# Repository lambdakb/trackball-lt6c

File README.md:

# LT6C 6 Keys Trackball

The LambdaKB LT6C is a re-creation of the [Ploopy Adept](https://ploopy.co/adept-trackball/) PCB and case as an easy to build DIY kit. The main goal was to build it using only off-the-shelf part and components that can be hand soldered relatively easily.

We set out to create a more affordable alternative to the original Adept trackball while retaining all its features, primarily for individuals in regions where purchasing the original kit isn't cost-effective (for example, shipping from the Ploopy store to Europe costs over €35 before import taxes).

## PCB

|             Front             |            Back             |
| :---------------------------: | :-------------------------: |
| [![PCB Front]][PCB Front PNG] | [![PCB Back]][PCB Back PNG] |

[PCB Front]: output/img/lt6c-pcb-top.svg
[PCB Front PNG]: output/img/lt6c-pcb-top.png
[PCB Back]: output/img/lt6c-pcb-bottom.svg
[PCB Back PNG]: output/img/lt6c-pcb-bottom.png

The PCB has been designed in [KiCad EDA 9.0](https://www.kicad.org/) using the [`kicad-lkbd`](https://github.com/lambdakb/kicad-lkbd) libraries.

You can preview the project files using [KiCanvas](https://kicanvas.org/?github=https%3A%2F%2Fgithub.com%2Flambdakb%2Ftrackball-lt6c%2Fblob%2Fmain%2Fpcb%2Flt6c-pcb.kicad_pro) directly in your browser and download the latest fabrication files for JLCPCB from the [latest release](https://github.com/lambdakb/trackball-lt6c/releases/latest/).

The exported schematic is also available under [`output/schematics`](output/schematics/).

### PCB Order

| Parameters                       | Value                  |
| -------------------------------- | ---------------------- |
| Base Material                    | FR4                    |
| Layers                           | 2                      |
| Dimensions                       | 62 × 64.4 mm           |
| PCB Thickness                    | 0.8 mm                 |
| PCB Color [^pcb-color]           | Green                  |
| Silkscreen                       | White                  |
| Surface Finish [^surface-finish] | Lead Free HASL or ENIG |
| Copper Weight                    | 1 oz                   |
| Via Covering                     | Tented                 |
| Min Via Hole Size                | 0.3 mm                 |
| Board Outline Tolerance          | ± 0.2 mm               |

[^pcb-color]: You can select any PCB color you want but manufacturers such as JLCPCB will charge you more for it as the combo 0.8 mm thickness, Lead Free HASL surface finish and alternative board color is pretty uncommon for them to produce.
[^surface-finish]: The "HASL (with lead)" option is extremely discouraged due to the risk of lead poisoning. We strongly recommend paying the premium for the "Lead Free HASL" option.

## Case

|                                                3D Render                                                 |
| :------------------------------------------------------------------------------------------------------: |
|  |

A 3D printed case is available under [`case`](case/), this is a simple modification of the original [Ploopy Adept's case](https://github.com/ploopyco/adept-trackball/tree/master/hardware/mechanicals) that adds clearance for the back of our PCB. No other major modification has been done it.

This includes:

- A pre-cconfigured [`3mf` file](case/lt6c-case.3mf) for Orca Slicer
- Printing instructions
- Individual STL files, STEP file, and the original Fusion 360 project archive

Feel free to modify the case to your liking, but please make sure to respect the original [license](./README.md#license) when doing so.

## BOM

| Part                          | Ref.                                 | Quantity | Remarks                                                                                                                                         |
| ----------------------------- | ------------------------------------ | :------: | ----------------------------------------------------------------------------------------------------------------------------------------------- |
| PCB                           | [LT6C PCB](./README.md#pcb)          |    1     | See [PCB](./README.md#pcb) section on how to order it.                                                                                          |
| 3D Printed Case               | [LT6C Case](./case/README.md)        |    1     | 3D Printed case adapted from the [Adept Trackball case]. Make sure to check its individual [BOM](case/README.md#bom) for the required hardware. |
| 44 mm Trackball               | Any [1.75" Snooker Ball]             |    1     | The trackball ball itself, any 1.75" snooker / billiard ball should work.                                                                       |
| XIAO RP2040 Controller        | [SeeedStudio XIAO RP2040]            |    1     | Main controller for QMK/Vial.                                                                                                                   |
| Micro Switches                | [D2LS-21 SMD Micro Switch]           |    6     | Micro switches for mouse buttons.                                                                                                               |
| PMW3360 Optical Sensor & Lens | [PMW3360DM-T2QU + LM19-LSI]          |    1     | Optical mouse sensor and lens used to detect trackball movement.                                                                                |
| 1.8V DO                       | [TPS76318 Fixed 1.8V LDO (SOT-23-5)] |    1     | Power regulator for optical sensor.                                                                                                             |
| 1uF Capacitor                 | [0805 SMD Ceramic Capacitor]         |    1     | Required by the optical sensor LDO.                                                                                                             |
| 4.7uF Capacitors              | [0805 SMD Ceramic Capacitor]         |    2     | Power filtering capacitor for optical sensor and required LDO.                                                                                  |
| 100nF Capacitors              | [0805 SMD Ceramic Capacitor]         |    1     | Power filtering for the optical sensor.                                                                                                         |
| 10K Ω Resistor                | [0805 SMD Resistor]                  |    1     | Required by the optical sensor.                                                                                                                 |
| 39 Ω Resistor                 | [0805 SMD Resistor]                  |    1     | Required by the optical sensor.                                                                                                                 |

[Adept Trackball case]: https://github.com/ploopyco/adept-trackball/tree/master/hardware/mechanicals
[1.75" Snooker Ball]: https://amzn.eu/d/hGChcvq
[SeeedStudio XIAO RP2040]: https://www.seeedstudio.com/XIAO-RP2040-v1-0-p-5026.html
[D2LS-21 SMD Micro Switch]: https://www.aliexpress.com/item/1005003435671261.html
[PMW3360DM-T2QU + LM19-LSI]: https://www.aliexpress.com/item/4000904265601.html?
[TPS76318 Fixed 1.8V LDO (SOT-23-5)]: https://www.aliexpress.com/item/1005007852956393.html
[0805 SMD Ceramic Capacitor]: https://www.aliexpress.com/item/32812155708.html
[0805 SMD Resistor]: https://www.aliexpress.com/item/32847143167.html

## Firmware

Firmware has been built using [Vial](https://get.vial.today/), a fork of [QMK](https://qmk.fm) allowing configuration through a nice GUI.

|                                                        Layout                                                         |
| :-------------------------------------------------------------------------------------------------------------------: |
|  |

Sources are available in our own [`lambdakb/vial-qmk`](hhttps://github.com/lambdakb/vial-qmk/tree/lambdakb/keyboards/lambdakb/lt6c) repository and can be built using the [QMK CLI](https://docs.qmk.fm/cli).

```sh
# Clone the repository
git clone --recursive https://github.com/lambdakb/vial-qmk.git
# Compile the firmware
cd vial-qmk
qmk compile -kb lambdakb/lt6c -km vial
# Shoudl generate a `lambdakb_lt6c_vial.uf2` file at the root of the repository.
```

To flash the firmware to your trackball, follow the following steps:

- Put the XIAO RP2040 in Bootloader mode by holding the BOOT button while plugging the USB cable (see [official guide](https://wiki.seeedstudio.com/XIAO-RP2040/#enter-bootloader-mode) if you need help).
- Mount the `RPI-RP2` drive on your computer.
- Copy or drag and drop the `lambdakb_lt6c_vial.uf2` file to the `RPI-RP2` drive.
- The trackball should now reboot, and the firmware should be flashed.
- Open the [Vial Desktop Application](https://config.vial.today/) or [Vial Web App](https://vial.rocks/app/) to configure the trackball.

> [!NOTE]
> To allow the firmware to be updated without requiring disassembly, you can enter Bootloader mode by holding the bottom left key of the trackball and plugging the USB cable. This is only possible after the firmware has been flashed the first time.

## Attribution

This project is a complete reimplementation of the [Ploopy Adept trackball](https://ploopy.co/adept-trackball/) PCB using off-the-shelf components that are relatively easy to hand solder.

The provided [3D printed case](#case) is a modification of [the Adept's original case](https://github.com/ploopyco/adept-trackball/tree/master/hardware/mechanicals) with a bit more space at the back to fit the new controller on the PCB. It has otherwise not be modified.

The original concept and design were created by Ploopy, who have licensed it under the [CERN Open Hardware Licence Version 2 – Strongly Reciprocal (CERN-OHL-S-2.0)](https://github.com/ploopyco/adept-trackball/blob/master/LICENSE), which permits adaptations, as demonstrated in this project.

## License

This design is licensed under the [CERN Open Hardware Licence Version 2 – Strongly Reciprocal (CERN-OHL-S-2.0)](https://opensource.org/license/cern-ohl-s).

You are free to use, modify, and distribute this design for any purpose, provided that:

- **Attribution**: Appropriate credit is given, a link to the license is provided, and any modifications are clearly indicated.
- **Reciprocity**: Any derivative works must be released under the same license.

If you are a retailer or business interested in producing or selling this design or related products, I’d love to discuss it! Please feel free to reach out so we can explore potential arrangements.

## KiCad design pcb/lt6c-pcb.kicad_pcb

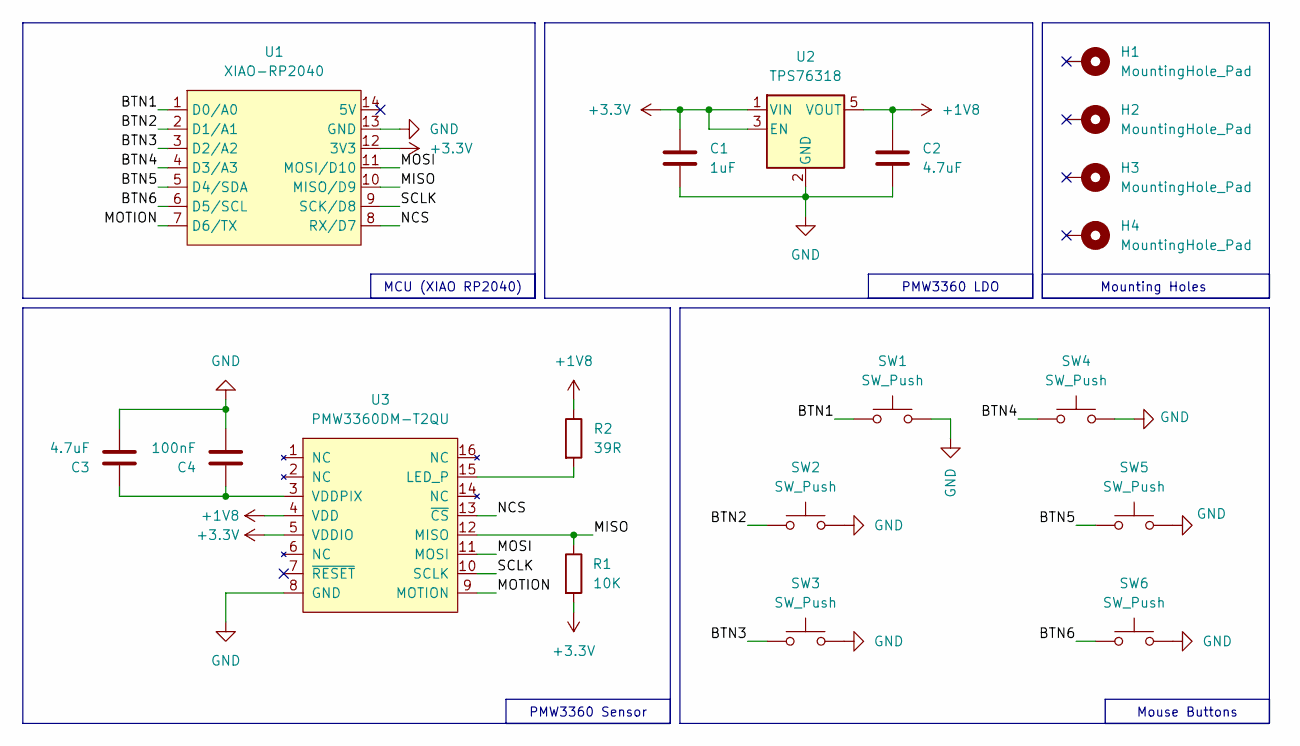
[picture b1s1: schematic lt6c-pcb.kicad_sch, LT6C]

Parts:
C1: 1uF; C_0805_2012Metric_Pad1.18x1.45mm_HandSolder; JLC 0805
C2, C3: 4.7uF; C_0805_2012Metric_Pad1.18x1.45mm_HandSolder; JLC 0805
C4: 100nF; C_0805_2012Metric_Pad1.18x1.45mm_HandSolder; JLC 0805
H1, H2, H3, H4: MountingHole_Pad; MountingHole_2.2mm_M2_ISO14580_Pad
R1: 10K; R_0805_2012Metric_Pad1.20x1.40mm_HandSolder; JLC 0805
R2: 39R; R_0805_2012Metric_Pad1.20x1.40mm_HandSolder; JLC 0805
SW1, SW2, SW3, SW4, SW5, SW6: SW_Push; SW_D2LS_OMR; JLC D2LS
U1: XIAO-RP2040; MCU_XIAO-RP2040
U2: TPS76318; SOT-23-5; JLC SOT-23-5
U3: PMW3360DM-T2QU; JLC DIP-16

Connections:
+1V8: C2.2, R2.1, U2.5 (VOUT), U3.4 (VDD)
+3.3V: C1.2, R1.2, U1.12 (3V3), U2.1 (VIN), U2.3 (EN), U3.5 (VDDIO)
/BTN1: SW1.1, U1.1 (D0/A0)
/BTN2: SW2.1, U1.2 (D1/A1)
/BTN3: SW3.1, U1.3 (D2/A2)
/BTN4: SW4.1, U1.4 (D3/A3)
/BTN5: SW5.1, U1.5 (D4/SDA)
/BTN6: SW6.1, U1.6 (D5/SCL)
/MISO: R1.1, U1.10 (MISO/D9), U3.12 (MISO)
/MOSI: U1.11 (MOSI/D10), U3.11 (MOSI)
/MOTION: U1.7 (D6/TX), U3.9 (MOTION)
/NCS: U1.8 (RX/D7), U3.13 (~CS)
/SCLK: U1.9 (SCK/D8), U3.10 (SCLK)
GND: C1.1, C2.1, C3.1, C4.1, SW1.2, SW2.2, SW3.2, SW4.2, SW5.2, SW6.2, U1.13 (GND), U2.2 (GND), U3.8 (GND)
unnamed: R2.2, U3.15 (LED_P)
unnamed: C3.2, C4.2, U3.3 (VDDPIX)

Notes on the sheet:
PMW3360 LDO
Mounting Holes
PMW3360 Sensor
MCU (XIAO RP2040)
Mouse Buttons

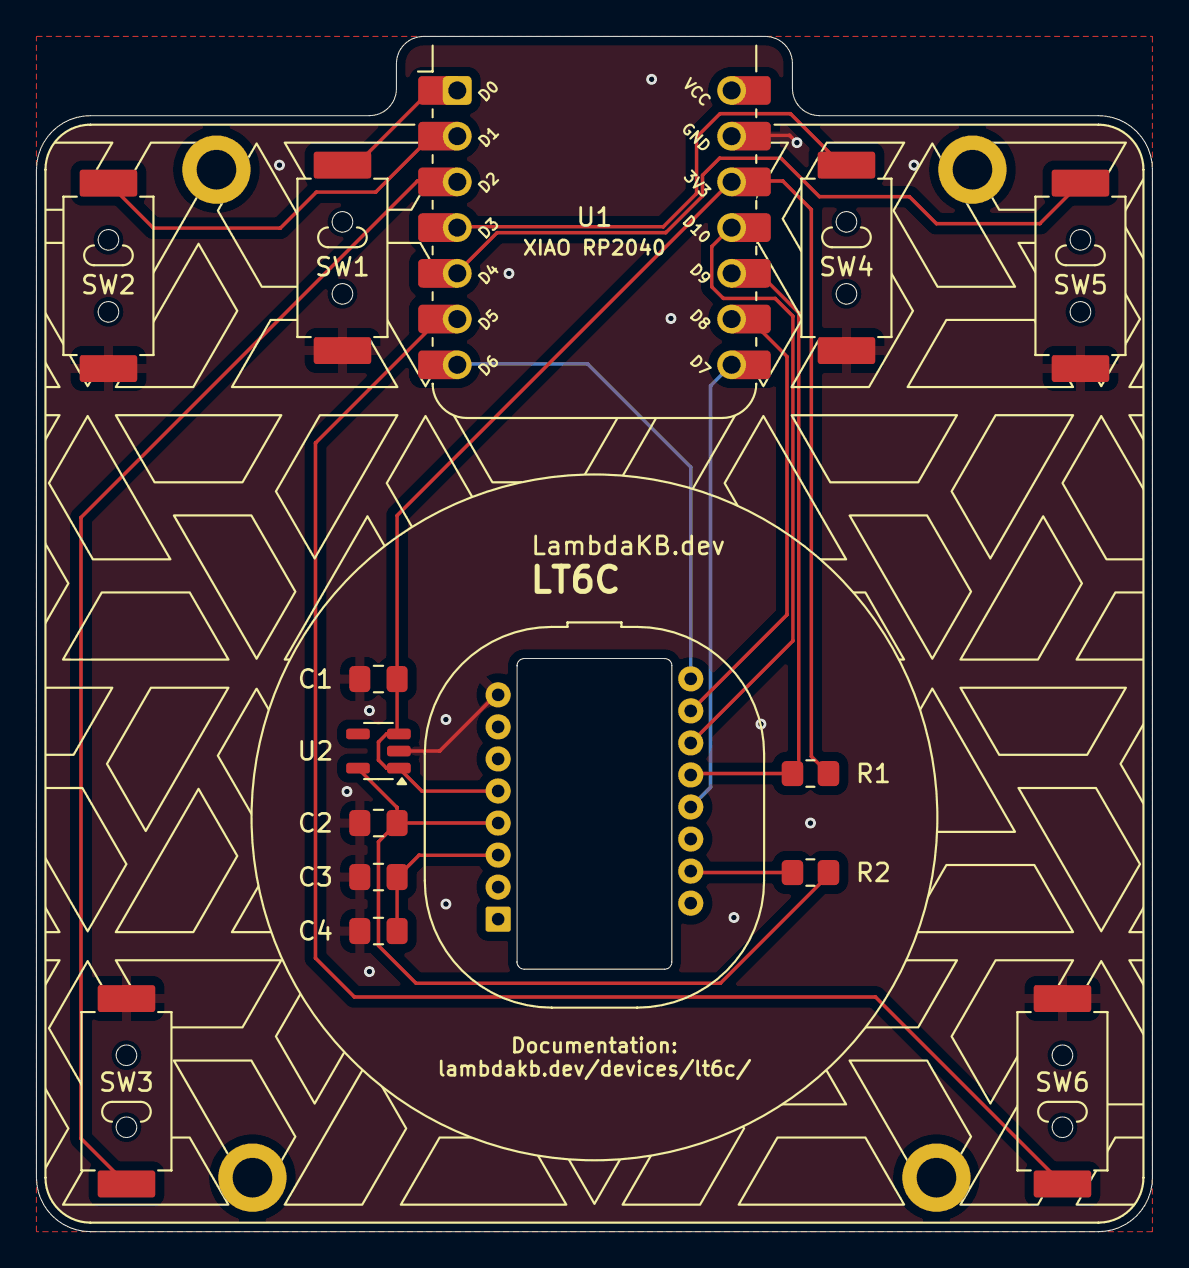
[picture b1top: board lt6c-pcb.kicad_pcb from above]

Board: 2 copper layers, 62.0 x 66.4 mm, 19 parts (1 on the bottom side), 16 nets.

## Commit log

2025-01-22 First version of XIAO RP2040 based Adept Clone
2025-01-23 Add silkscreen pattern and infos
2025-01-24 Update silkscreen
2025-01-26 Cleanup README.md
2025-01-29 Add pinouts to XIAO-RP2040 and cleanup silkscreen
2025-02-03 Fix ERC/DRC + update LKBD libraries
2025-02-04 Add attribution to the original Ploopy Adept
2025-02-04 Cleanup schematic and pcb
2025-02-06 Add BOM to README.md
2025-02-06 Add BOM to README.md (#1)
2025-02-06 Add missing snooker ball to BOM
2025-02-06 Fix U2 silkscreen positioning
2025-02-07 Add PCB order parameters table + switch color export to green
2025-02-07 Add PCB order parameters table + switch color export to green (#3)
2025-02-09 Fix README links
2025-02-09 Add 3DP case section in README and matching attribution
2025-02-11 Add case 3D model
2025-02-11 Add 3DP case based on the original Ploopy Adept Case (#2)
2025-03-17 Update case README and exports
2025-03-19 Fix typo in README.md
2025-03-19 Cleanup BTU mod README
2025-03-20 Cleanup case/README.md
2025-03-20 Add more BTU render
2025-03-20 Final Case Design + BTU Mod + Case README (#5)
    * Update case README and exports
    * Update README.md
    * Update case to latest version, add BTU mod and add render to case/README.md
    * Fix typo in README.md
    * Cleanup BTU mod README
    * Cleanup case/README.md
2025-03-20 Add info and link to the firmware
2025-03-20 Add info and link to the firmware (#6)
2025-03-20 Upgrade project to KiCad 9
2025-03-20 Upgrade project to KiCad 9 (#7)
2025-03-20 Update READMEs
2025-03-20 Add firmware build instruction and missing part to case BOM (#9)
2025-03-20 Update heatset insert hole size
2025-03-20 Write CNC Kitchen properly
2025-03-20 Update heatset insert hole size (#10)
2025-03-20 Update Case Print Profile
2025-03-20 Update Case Print Profile (#11)
2025-03-21 Remove brim from print profile
2025-03-21 Remove brim from print profile (#12)
2025-03-28 Update README & cleanup 3MF print profile (#13)
2025-05-13 Update LKBD libraries
2025-05-13 Update LKBD libraries (#14)

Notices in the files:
README.md:
License: CERN-OHL-S-2.0
